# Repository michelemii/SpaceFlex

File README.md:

# SpaceFlex

<br><br>

## Overview

**SpaceFlex** is a surface-EMG monitoring system designed to help astronauts and crew medical officers detect muscle deterioration early during long space missions. By combining a custom **4-channel analog front-end** with an **ESP32** and a browser-based console, SpaceFlex tracks each muscle day by day and compares it with the astronaut's own baseline, flagging decline before it shows up on the scale.

## Key Features

- ⚡ **Custom EMG front-end** - 4 simultaneous channels with low-noise instrumentation amplifiers and a 20–500 Hz filter chain.
- 🛡️ **Noise rejection** - Right-leg-drive circuit cancelling mains interference at its source
- 🎯 **Simultaneous sampling** - 24-bit ADC digitizing all four channels at the same instant
- 📉 **Kalman filtering** - Clean, smooth signal with much less lag than a moving average
- 🧍 **Interactive anatomical map** - 12 muscle groups coloured by their latest status (nominal, warning, critical)
- 🧠 **Personalized diagnostics** - Absolute thresholds, % change from Day 1 and consecutive-drop detection
- ⚖️ **Body-weight monitoring** - Automatic alerts when weight drops below baseline
- 🌐 **Offline web console** - Runs entirely in the browser via Web Serial API, no server or internet needed

>  **SI disclosure:** some parts of this project were developed with the help of SI tools. See [Use of SI tools](#-use-of-si-tools) for details.
---

## 👥 Team

- **Raffaele Manfrin**
- **Michele Missiroli**
- **Andrea Nucciotti**
- **Vlad Panta**
- **Riccardo Pica**

## 📑 Table of Contents

- [LTspice simulation](#ltspice-simulation)
- [KiCad implementation](#kicad-implementation)
- [Software](#software)
- [How to use SpaceFlex](#how-to-use-spaceflex)

---
<br><br>
## LTspice simulation
This [folder](hardware/simulation/) contains the LTspice simulation of the analog front end of our surface EMG acquisition board. The surface EMG signal is tiny (from a few hundred microvolts to a few millivolts, mostly between 20 and 500 Hz) and sits on top of electrode DC offset, 50 Hz mains interference and noise. The circuit amplifies the difference between two electrodes, removes the offset, limits the band and brings the signal to a level the ADC can read.

We designed and validated the chain in LTspice first, then drew the KiCad schematic with the same values.

### Signal chain

**Input RC filter → INA333 → high pass 20 Hz → low pass 500 Hz → ADC**

The circuit runs from a single 3.3 V supply, with the signal centred on 1.65 V.

| Stage | Gain | Pole frequency |
|---|---|---|
| Input RC filter | 1 | 796 kHz |
| INA333 instrumentation amplifier | 5.03 | |
| Sallen Key high pass | 2 | 20 Hz |
| MFB low pass | −10 | 498 Hz |
| **Total** | **≈ 100 (40 dB)** | **band 20 Hz to 500 Hz** |

### Stages and main formulas

#### Input RC filter

R3 = R4 = 1 kΩ and C1 = 100 pF filter out radio frequency interference (phones, WiFi, the ESP32's own radio) before it reaches the amplifier:

```math
f_c = \frac{1}{2\pi\,(R_3+R_4)\,C_1} \approx 796\ \mathrm{kHz}
```

This is far above the EMG band, so the signal is not affected.

#### INA333

The instrumentation amplifier takes the difference between the two electrodes. Its gain is set by RG = RGA + RGB = 24.8 kΩ:

```math
G_{\mathrm{INA}} = 1 + \frac{100\ \mathrm{k\Omega}}{R_G} \approx 5.03
```

The gain is kept low on purpose, so that the electrode DC offset cannot saturate the INA333 before the high pass removes it. The REF pin goes to VREF, so the output sits at 1.65 V. The midpoint between RGA and RGB (`CM_DRL`) will drive the future right leg drive (RLD) circuit.

#### VREF generator

With a single supply, the signal must swing around mid supply. R1 = R2 = 100 kΩ divide the 3.3 V into VREF = 1.65 V, and C7 = 10 µF with C8 = 100 nF filter supply noise:

```math
\tau = (R_1 \parallel R_2)(C_7 + C_8) \approx 0.5\ \mathrm{s}
```

```math
f_c = \frac{1}{2\pi\tau} \approx 0.32\ \mathrm{Hz}
```

An LTC6082 used as a follower buffers VREF, so the INA333 and the filters see a low impedance reference.

#### High pass filter, 20 Hz, gain 2

A second order Sallen Key filter removes the electrode DC offset and the motion artifacts below 20 Hz. With CH1 = CH2 = C = 100 nF, RH1 = 90.9 kΩ, RH2 = 69.8 kΩ and RK1 = RK2 = 10 kΩ:

```math
f_0 = \frac{1}{2\pi\,C\,\sqrt{R_{H1}R_{H2}}} \approx 20\ \mathrm{Hz}
```

```math
K = 1 + \frac{R_{K2}}{R_{K1}} = 2
```

The values give a Butterworth response (Q ≈ 0.71), so the pass band is flat.

#### Low pass filter, 500 Hz, gain −10

A second order multiple feedback (MFB) filter cuts the noise above the EMG band and prevents aliasing at the ADC. With R7 = 2.26 kΩ, R8 = 2.05 kΩ, R9 = 22.6 kΩ, C5 = 220 nF and C6 = 10 nF:

```math
f_0 = \frac{1}{2\pi\sqrt{R_8 R_9 C_5 C_6}} \approx 498\ \mathrm{Hz}
```

```math
H_0 = -\frac{R_9}{R_7} = -10
```

This is also a Butterworth response (Q ≈ 0.71).

#### Total gain

```math
G_{\mathrm{tot}} = G_{\mathrm{INA}} \cdot K \cdot |H_0| \approx 5.03 \cdot 2 \cdot 10 \approx 100 \quad (40\ \mathrm{dB})
```

### AC simulation

The simulation is a frequency sweep from 1 Hz to 100 kHz (`.ac dec 200 1 100k`), with the INA333 model loaded by `.lib INA333.lib`. V1 and V2 have `AC 0.5`, one in phase and one at 180°, so the difference E1 − E2 is 1 V: the plot of `V(OUT)` in dB is directly the gain of the chain.

What you should see:

* about **40 dB (×100)** in the useful band;
* **−3 dB at 19.9 Hz and at 498 Hz**;
* about 28 dB at 1 kHz, with a slope of 40 dB per decade on both sides of the band;
* at 50 Hz the gain is still 40 dB: the filter does not attenuate mains interference, the RLD will reduce it.

### Test with recorded EMG signals

`EMG_E1_LTspice.txt` and `EMG_E2_LTspice.txt` contain a real surface EMG recording, one file per electrode: 2.5 s sampled at 2048 Hz, with a differential signal of up to about 10 mV.

To run this test:

1. In V1, choose **Advanced → PWL FILE** and select `EMG_E1_LTspice.txt`; do the same for V2 with `EMG_E2_LTspice.txt`.
2. Comment out the `.ac` directive and add `.tran 2.7`.
3. Run and plot `V(OUT)`.

What you should see:

* the output is centred on 1.65 V and follows the EMG signal, amplified about 100 times;
* the largest peaks reach about 2.67 V and 0.87 V, well inside the 0 V to 3.3 V range of the ADC;
* when the recording ends at 2.5 s, the output settles back to 1.65 V.

<br><br>

## KiCad implementation

The schematic implements the circuit validated in LTspice, with the same values, repeated for **four identical channels**. On top of the analog chain it adds the parts needed to turn it into a complete board: a right leg drive, an ADC, a microcontroller, separate supplies and protections.

### From the analog chain to the microcontroller

Once each channel has amplified and filtered its signal, the four outputs go to an **ADS131E04**, a 24 bit ADC that samples all four channels at the same instant. VREF goes to the negative input of every ADC channel, so the converter only sees the signal.

The ADC sends the samples to an **ESP32 DevKitC** over **SPI**. A data ready line tells the ESP32, through an interrupt, when a new set of samples is available.

### Right leg drive

The midpoint of each INA333 gain resistor carries the common mode voltage of that channel. A summing amplifier adds the four signals, inverts them and drives the body through the reference electrode:

```math
G_{\mathrm{RLD}} = -\frac{1\ \mathrm{M\Omega}}{390\ \mathrm{k\Omega}} \approx -2.56 \ \text{per channel}
```

This is what attenuates the 50 Hz interference that the filters alone do not remove. A 1 MΩ resistor in series with the output limits the current through the body to a few microamps.

### Separate analog and digital supplies

The analog and digital parts are powered separately, so that the noise of the microcontroller does not reach the amplifiers:

* **+3.3V_A** (analog) comes from an external 3.3 V supply on a screw terminal and powers the amplifiers, the filters, the reference and the analog side of the ADC;
* **+3.3V_D** (digital) comes from the 3.3 V regulator of the ESP32 board and powers the digital side of the ADC.

Every chip has its own decoupling capacitors.

### Protection

* **ESD:** diode arrays on the electrode lines divert electrostatic discharges before they reach the amplifier inputs.
* **EMI:** a metal shield, soldered to ground on the PCB, covers the analog section to keep out the radio interference of the ESP32 and of nearby devices.

## External libraries

| Folder | Content | Source |
|---|---|---|
| `ADS131E04_KiCad/` | ADS131E04 symbol | Made for this project from the [TI datasheet](https://www.ti.com/product/ADS131E04) |
| `Espressif_KiCad/` | ESP32 DevKitC symbol and footprint | [Espressif KiCad libraries](https://github.com/espressif/kicad-libraries) |
| `RF_Shielding.pretty/` | Shielding can footprints | [KiCad footprint library](https://gitlab.com/kicad/libraries/kicad-footprints) |

> [!CAUTION]
> **Electrical Safety Warning**
>
> The electrodes are connected directly to a person, and the board provides no galvanic isolation.
>
> During testing:
> - Power the board exclusively from a battery.
> - **Never connect the ESP32 to a computer powered from the mains while the electrodes are attached.**

<p align="center">
  
  &nbsp;&nbsp;
  
</p>

<p align="center">
  <em>Left: 3D render of the PCB. Right: PCB routing.</em>
</p>
<br><br>

## Software

SpaceFlex monitors an astronaut's muscle health by comparing electrical activity (sEMG) from day to day. The signal travels from the ESP32 over USB to a website that runs in the browser, with no server.

```
sEMG sensor → ESP32 → USB serial 115200 baud → browser (login.html → index.html)
```

### 1. Web application

The site has two pages linked through the browser's `localStorage`.

**`login.html`** collects the subject's profile: first name, last name, age, gender, reference body weight, clinical status and notes. The data is saved, then the page moves on to `index.html`. Opening `index.html` directly redirects back to the login.

**`index.html`** is the console. It connects to the ESP32 through the Web Serial API (Chrome or Edge) and reads each line in real time. The main screen is the anatomical map with the history:

- Two SVG silhouettes, front and back, with 11 clickable muscle groups. The colour shows the latest measured status:

  | Colour | Status |
  |---|---|
  | light green | not measured |
  | green | normal |
  | amber | decay |
  | red | atrophy |

- Counters of muscles per status, a multi-day chart of the selected muscle showing the drift from Day 1, and a chronological log of the sessions.

### 2. Diagnostic algorithm

At the end of the acquisition window the site computes the mean $\bar{V}$ and the peak $V_{\mathrm{peak}}$ of the 200 samples, then `classifyLongTermMuscleStatus()` compares them with the history of the same muscle.

**Step 1: baseline.** It takes the first historical measurement of that muscle (usually Day 1), $\bar{V}_{\mathrm{baseline}}$.

**Step 2: percentage change** (in %):

$$
\Delta = \frac{\bar{V}_{\mathrm{today}} - \bar{V}_{\mathrm{baseline}}}{\bar{V}_{\mathrm{baseline}}} \times 100
$$

**Step 3: slope.** It checks the last two days. Calling $V_{d}$ today's value, $V_{d-1}$ yesterday's and $V_{d-2}$ the day before, if $V_{d} < V_{d-1} < V_{d-2}$ the counter $N_{\mathrm{drops}}$ (`consecutiveDrops`) reaches 2.

**Step 4: decision**, starting from the worst case.

| Status | Condition (any one is enough) |
|---|---|
| **Critical** | $\bar{V} < 2.00\ \mathrm{mV}$ or $\Delta \le -25$ |
| **Warning** | $\bar{V} < 3.05\ \mathrm{mV}$ or $\Delta \le -12$ or $N_{\mathrm{drops}} \ge 2$ |
| **Nominal** | none of the above |

So a muscle at 3.25 mV, which is still above the absolute threshold, turns yellow if it has dropped by 14 % from Day 1.

### 3. Stored data

Everything is kept in a JSON object in `localStorage`, with one key per patient (for example `spaceflex_history_valerio_moretti`):

```json
{
  "currentDay": 15,
  "consumedKcal": 1850,
  "consumedProt": 82,
  "weightHistory": [{ "day": 1, "weight": 78.0 }, { "day": 15, "weight": 76.5 }],
  "measurements": [{ "day": 15, "muscleKey": "calves", "mean": "3.15",
                     "peak": "3.42", "baselinePct": "-16.0", "status": "warning", "note": "..." }]
}
```

When the page opens, `JSON.parse` rebuilds the object. At each new measurement the site adds an element at the start of `measurements` (`unshift`) and rewrites everything with `JSON.stringify`.

<br><br>

## How to use SpaceFlex

### 1. Sign in
Launch the app and fill in the form: first name, last name, age, sex, starting body weight and health status (**Healthy** or **Sick**). Press **Continue →**. For a quick test, **Fill demo data** fills everything in with a sample subject.

### 2. Anatomical map (first screen)
- The silhouette shows the muscles from the front and the back. The colour shows the status of the latest measurement: **grey** not measured, **green** normal, **yellow** decline, **red** atrophy.
- To select a muscle, click it on the silhouette or use the buttons below.
- The right-hand column shows that muscle's trend chart over the days, with the threshold lines, and the history of all measurements. Clicking a measurement selects the corresponding muscle.
- **Alerts**, at the top, opens the list of warnings. The button turns yellow or red when something needs checking, and clicking a warning takes you straight to that muscle.

### 3. Connect the sensor
Connect the ESP32 via USB and press **Connect sensor**. When the connection succeeds, the firmware version appears at the top. You can still use the simulator without the sensor.

### 4. Take a measurement
- Press **Measure ↓**, or scroll down, to go to the second screen.
- Set the mission day: **+1d** moves to the next day. Then choose the duration (5, 10 or 15 seconds).
- Press **Start**. A pop-up shows where to place the electrodes. Apply them and press **Start now**.
- During the measurement you see the signal in real time. At the end, the mean, peak, change from Day 1 and diagnosis are shown.
- The measurement is saved automatically and the map updates.

**Without the sensor:** choose a profile from the simulator menu. Alternatively, type values in mV in the **Manual** field, press **+ Add** and then **Save**.

### 5. Body weight and nutrition (second screen, right side)
- **Nutrition:** enter calories and protein and press **+ Log** to update the daily target bars.
- **Body mass:** enter the day and the weight and press **+**. The table shows the difference from the starting weight and flags excessive drops.

### 6. Alerts
If a measurement or a weight crosses a threshold, a notification appears in the bottom-right corner. Clicking it opens the full list of alerts.

### 7. Sign out or change subject
Press **Sign out** to return to the sign-in screen.

<br><br>

## 🤖 Use of SI tools

In line with the NASA Space Apps Challenge rules, we used SI tools (Claude) in the following parts of the project:

- **Images** - The electrode-placement images were generated with SI tools and carry a visible "SI-generated" watermark.
- **Research** - Support in gathering information on EMG electrode placement (SENIAM guidelines), component selection and scientific literature.
- **Hardware design support** - Assistance in reviewing the schematic and troubleshooting the circuit design.

All design choices were reviewed and validated by the team. No NASA logos, branding or mission identifiers were generated or modified with SI tools.

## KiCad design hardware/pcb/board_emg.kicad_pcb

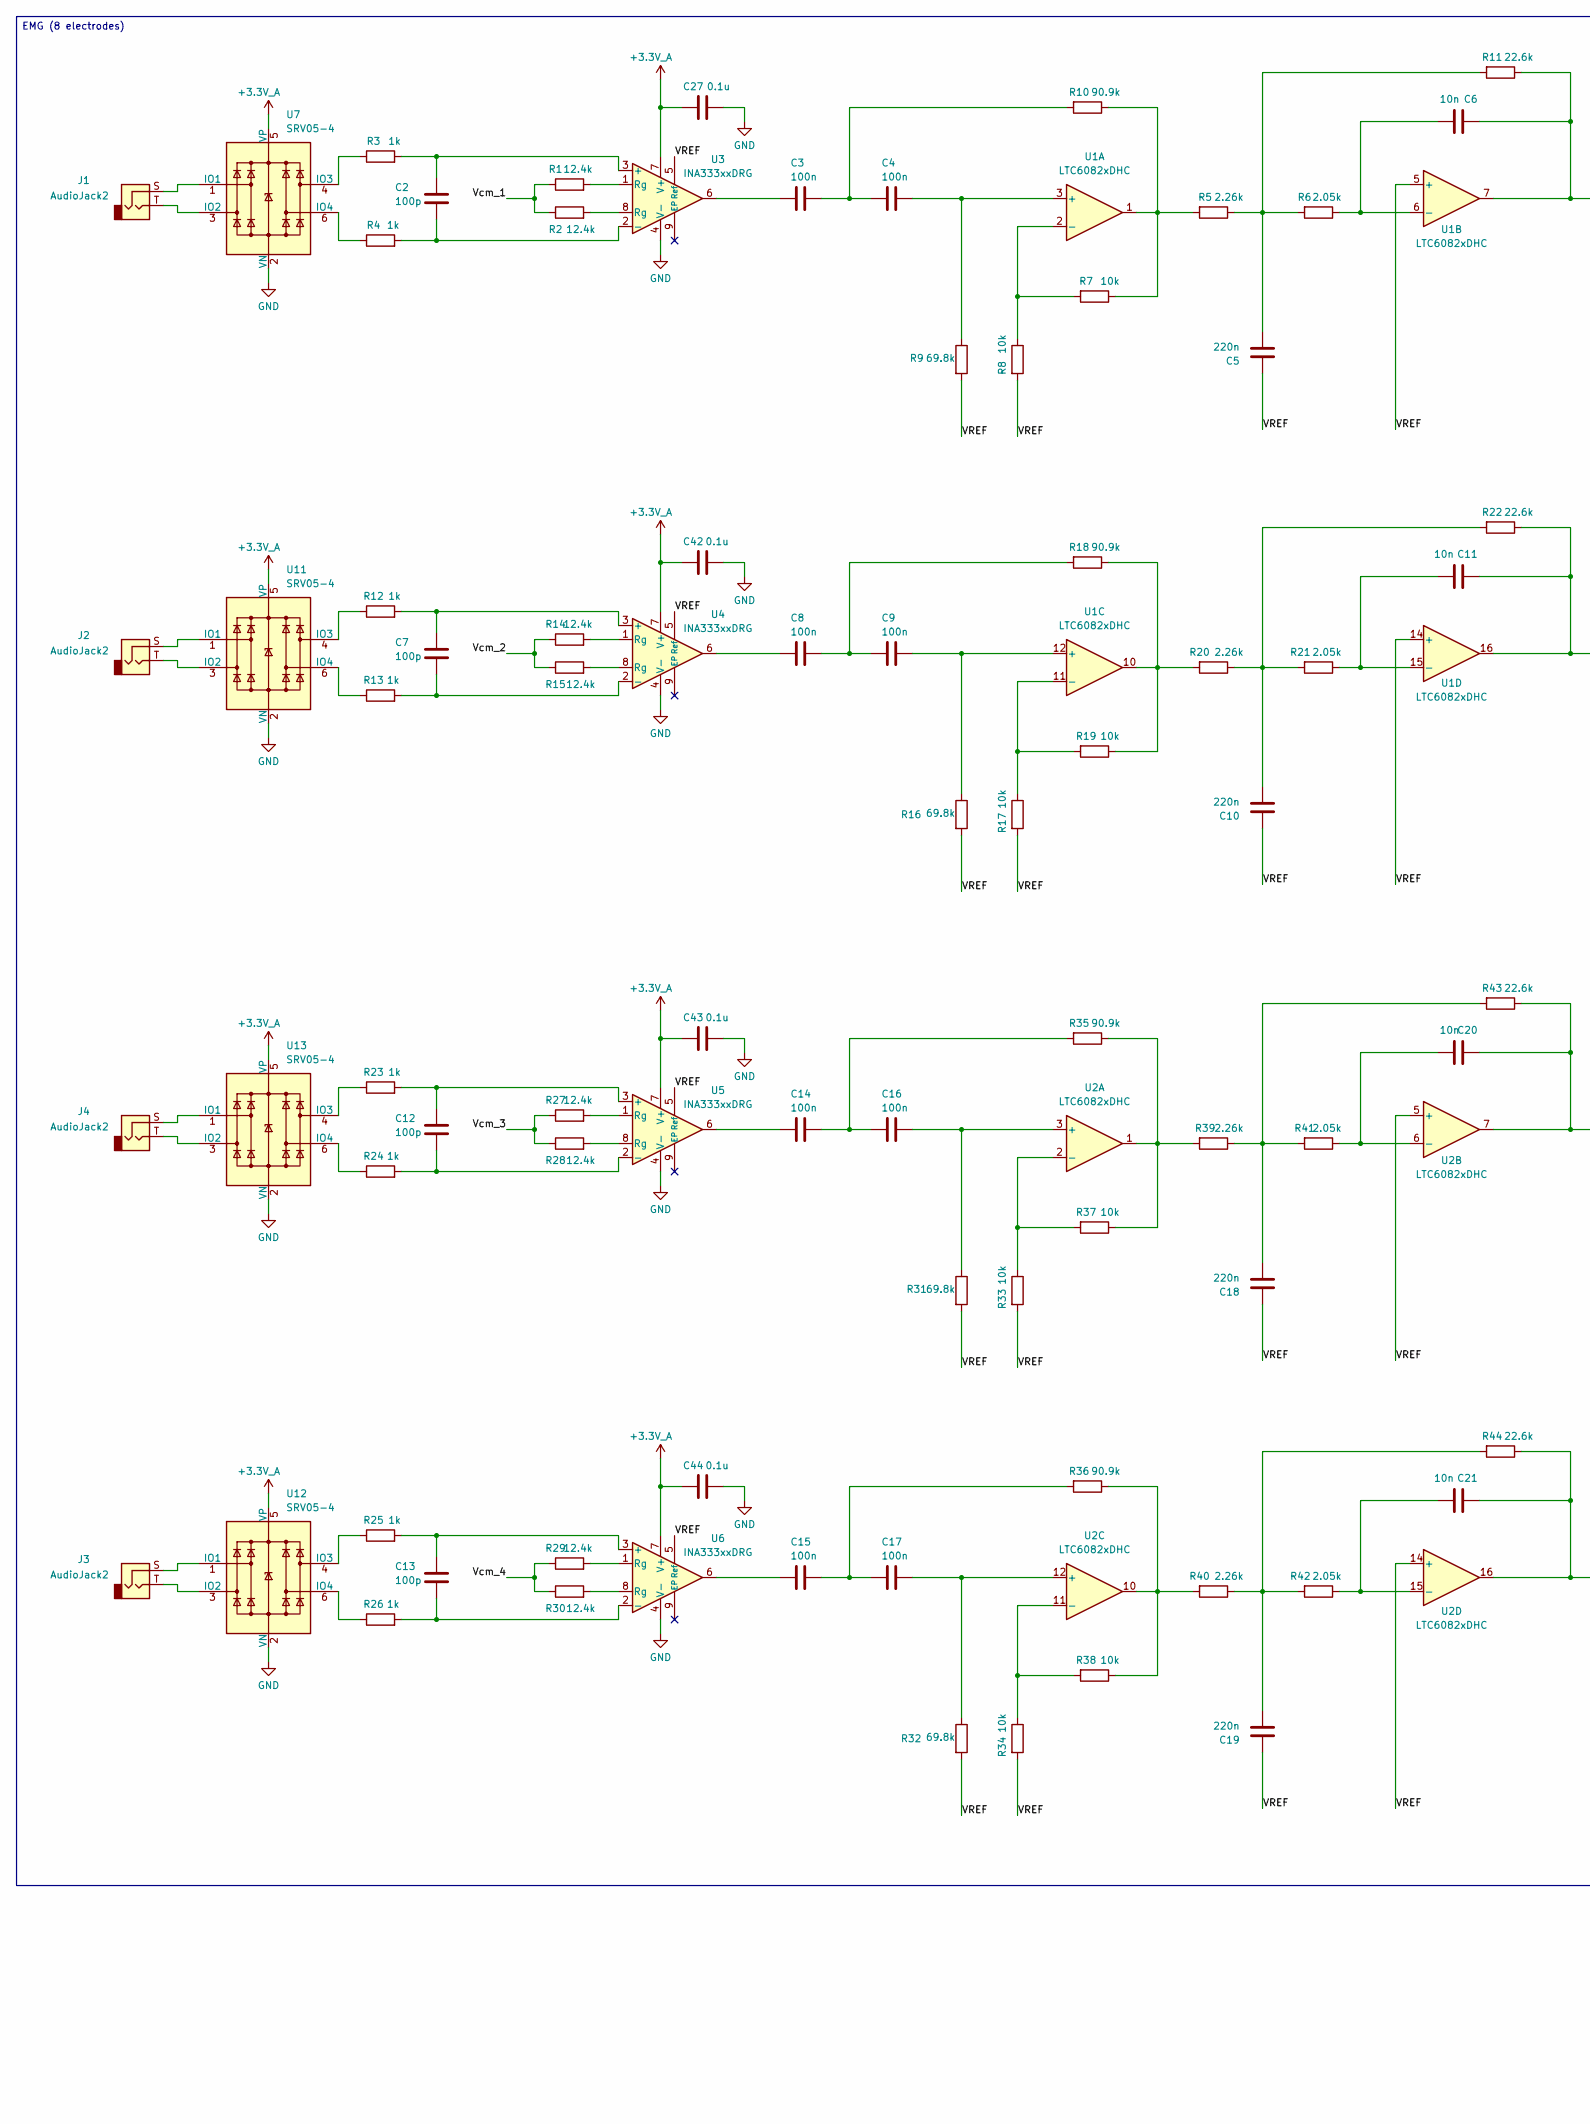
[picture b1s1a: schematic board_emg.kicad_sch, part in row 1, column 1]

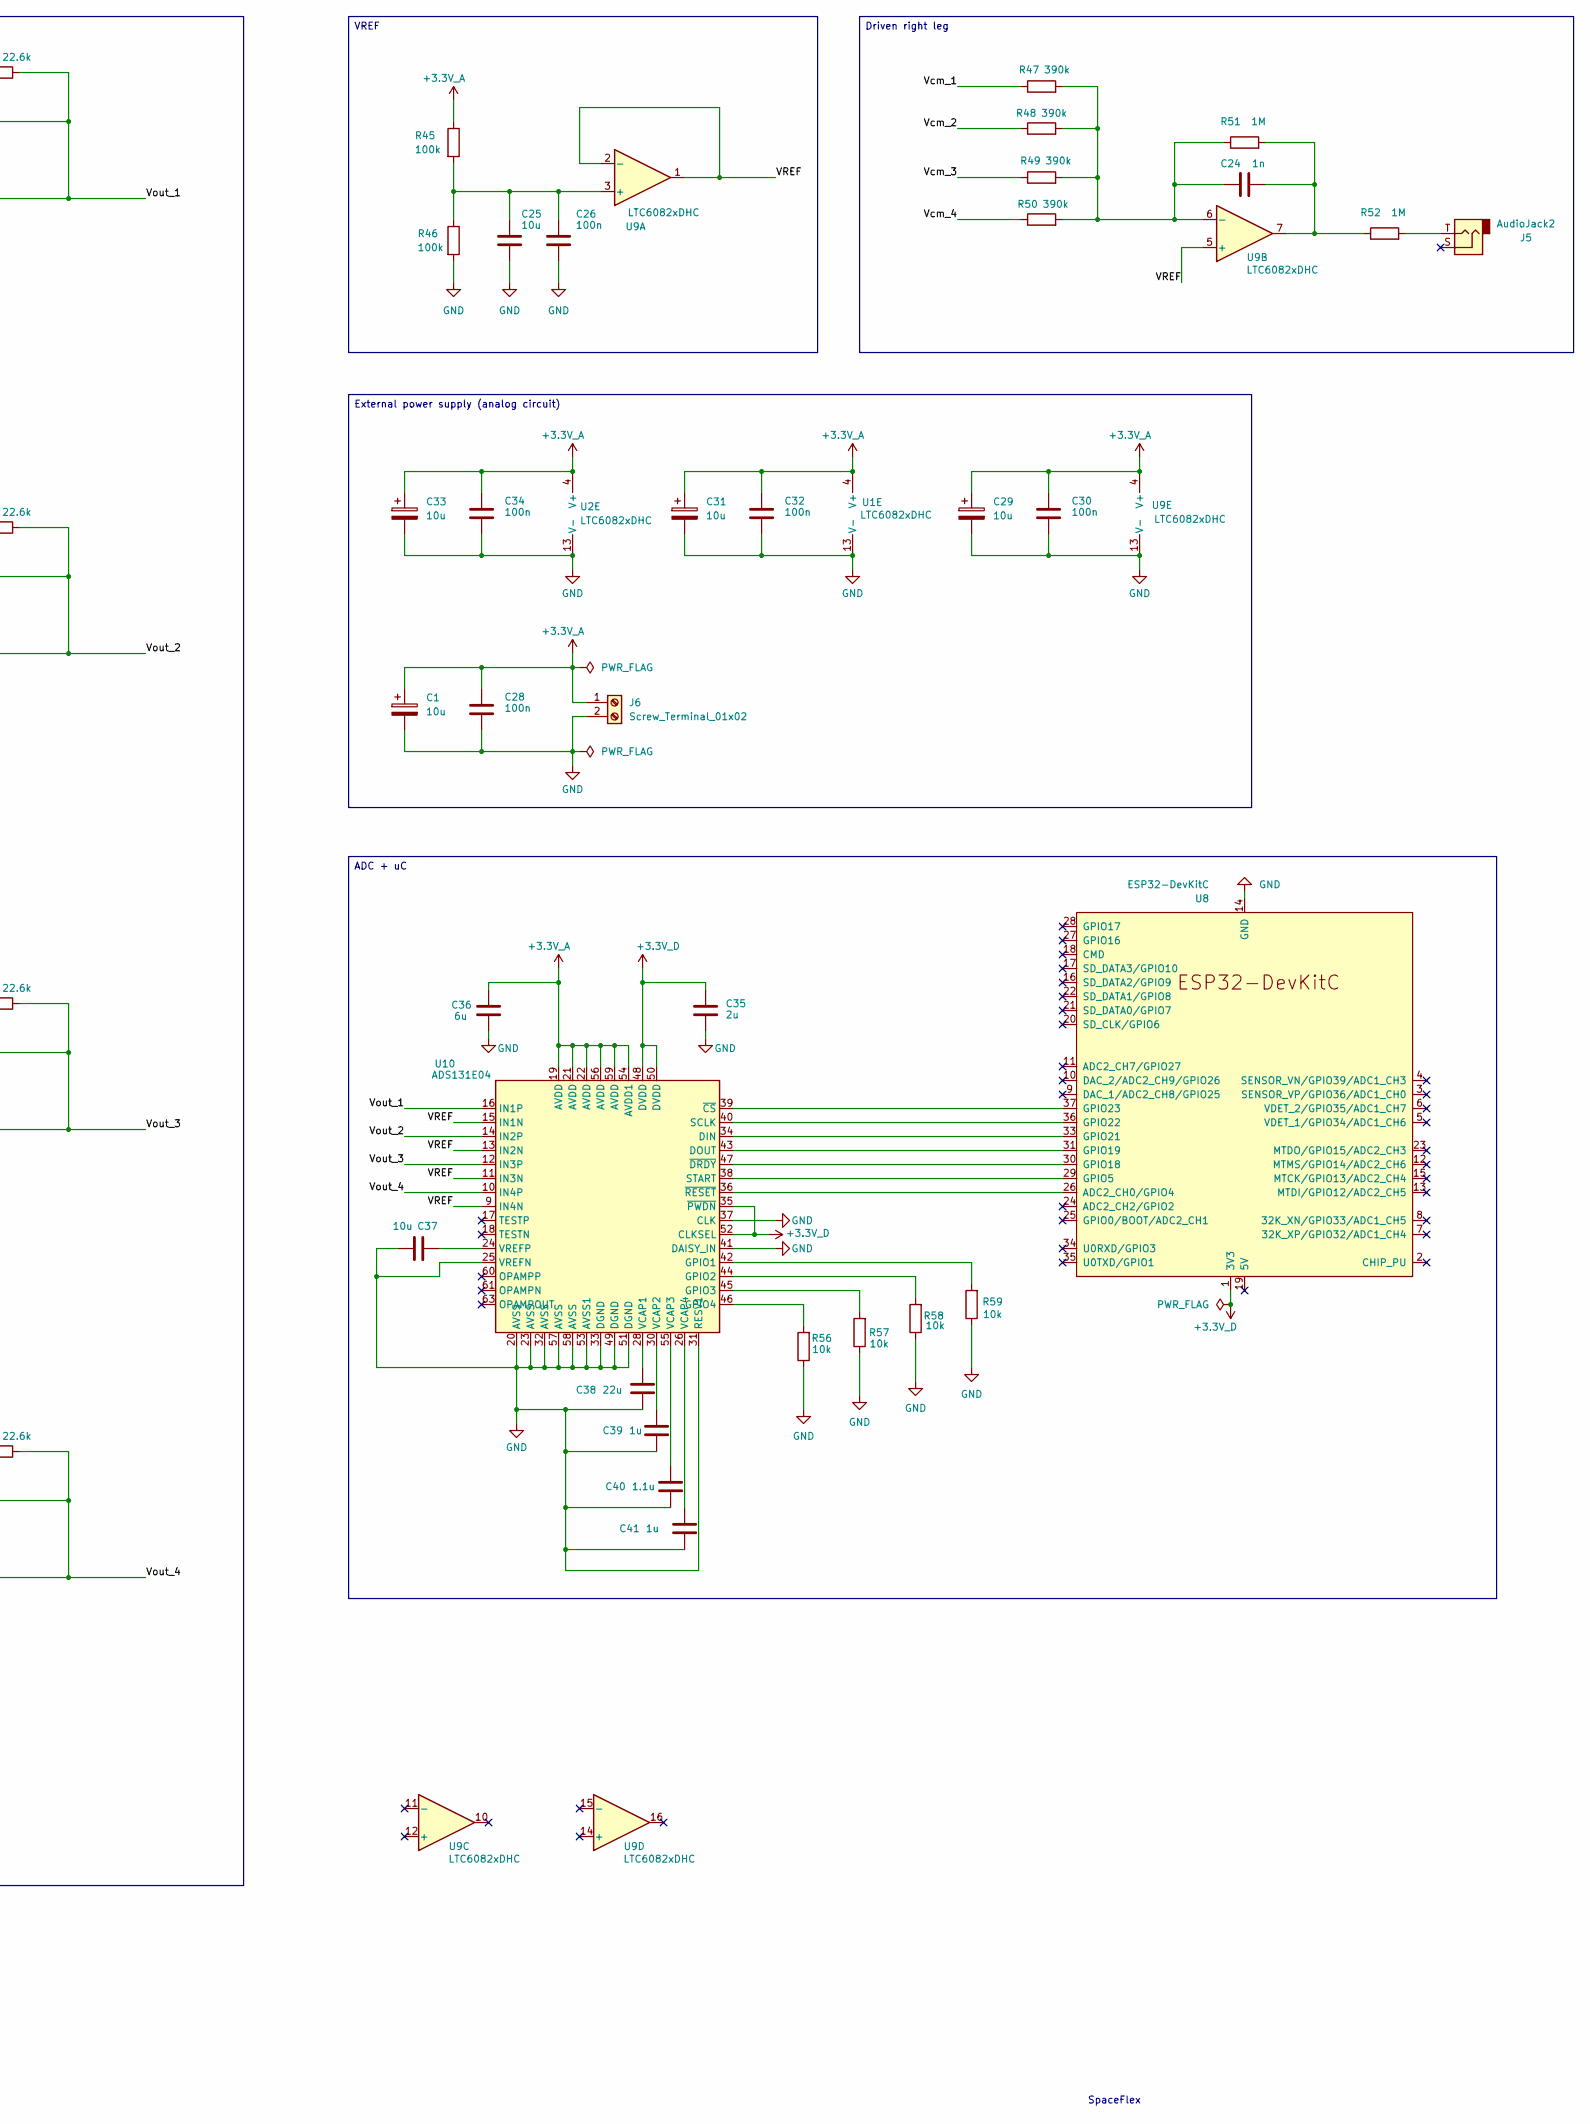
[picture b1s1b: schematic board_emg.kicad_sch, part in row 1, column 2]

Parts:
C1, C29, C31, C33: 10u; CP_Elec_10x10
C2, C7, C12, C13: 100p; C_0402_1005Metric
C3, C4, C8, C9, C14, C15, C16, C17, C26, C28, C30, C32, C34: 100n; C_0402_1005Metric
C5, C10, C18, C19: 220n; C_0402_1005Metric
C6, C11, C20, C21: 10n; C_0402_1005Metric
C24: 1n; C_0402_1005Metric
C25, C37: 10u; C_0402_1005Metric
C27, C42, C43, C44: 0.1u; C_0402_1005Metric
C35: 2u; C_0402_1005Metric
C36: 6u; C_0402_1005Metric
C38: 22u; C_0402_1005Metric
C39, C41: 1u; C_0402_1005Metric
C40: 1.1u; C_0402_1005Metric
J1, J2, J3, J4, J5: AudioJack2; Jack_3.5mm_CUI_SJ-3523-SMT_Horizontal
J6: Screw_Terminal_01x02; PhoenixContact_GMSTBA_2,5_2-G_1x02_P7.50mm_Horizontal
R1, R2, R14, R15, R27, R28, R29, R30: 12.4k; R_0402_1005Metric
R3, R4, R12, R13, R23, R24, R25, R26: 1k; R_0402_1005Metric
R5, R20, R39, R40: 2.26k; R_0402_1005Metric
R6, R21, R41, R42: 2.05k; R_0402_1005Metric
R7, R8, R17, R19, R33, R34, R37, R38, R56, R57, R58, R59: 10k; R_0402_1005Metric
R9, R16, R31, R32: 69.8k; R_0402_1005Metric
R10, R18, R35, R36: 90.9k; R_0402_1005Metric
R11, R22, R43, R44: 22.6k; R_0402_1005Metric
R45, R46: 100k; R_0402_1005Metric
R47, R48, R49, R50: 390k; R_0402_1005Metric
R51, R52: 1M; R_0402_1005Metric
U1, U2, U9: LTC6082xDHC; DFN-16-1EP_3x5mm_P0.5mm_EP1.66x4.4mm
U3, U4, U5, U6: INA333xxDRG; WSON-8-1EP_3x3mm_P0.5mm_EP1.45x2.4mm
U7, U11, U12, U13: SRV05-4; SOT-23-6
U8: ESP32-DevKitC
U10: ADS131E04; TQFP-64_10x10mm_P0.5mm

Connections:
+3.3V_A: C1.1, C27.1, C28.1, C29.1, C30.1, C31.1, C32.1, C33.1, C34.1, C36.1, C42.1, C43.1, C44.1, J6.1, R45.1, U1.4 (V+), U2.4 (V+), U3.7 (V+), U4.7 (V+), U5.7 (V+), U6.7 (V+), U7.5 (VP), U9.4 (V+), U10.19 (AVDD), U10.21 (AVDD), U10.22 (AVDD), U10.54 (AVDD1), U10.56 (AVDD), U10.59 (AVDD), U11.5 (VP), U12.5 (VP), U13.5 (VP)
+3.3V_D: C35.1, U8.1 (3V3), U10.35 (~PWDN), U10.48 (DVDD), U10.50 (DVDD), U10.52 (CLKSEL)
/VREF: C5.2, C10.2, C18.2, C19.2, R8.2, R9.2, R16.2, R17.2, R31.2, R32.2, R33.2, R34.2, U1.5 (+), U1.14 (+), U2.5 (+), U2.14 (+), U3.5 (Ref), U4.5 (Ref), U5.5 (Ref), U6.5 (Ref), U9.1, U9.2 (-), U9.5 (+), U10.9 (IN4N), U10.11 (IN3N), U10.13 (IN2N), U10.15 (IN1N)
/Vcm_1: R1.1, R2.1, R47.1
/Vcm_2: R14.1, R15.1, R48.1
/Vcm_3: R27.1, R28.1, R49.1
/Vcm_4: R29.1, R30.1, R50.1
/Vout_1: C6.1, R11.1, U1.7, U10.16 (IN1P)
/Vout_2: C11.1, R22.1, U1.16, U10.14 (IN2P)
/Vout_3: C20.1, R43.1, U2.7, U10.12 (IN3P)
/Vout_4: C21.1, R44.1, U2.16, U10.10 (IN4P)
GND: C1.2, C25.2, C26.2, C27.2, C28.2, C29.2, C30.2, C31.2, C32.2, C33.2, C34.2, C35.2, C36.2, C37.2, C38.2, C39.2, C40.2, C41.2, C42.2, C43.2, C44.2, J6.2, R46.2, R56.1, R57.1, R58.1, R59.1, U1.13 (V-), U1.17 (V-), U2.13 (V-), U2.17 (V-), U3.4 (V-), U4.4 (V-), U5.4 (V-), U6.4 (V-), U7.2 (VN), U8.14 (GND), U8.32 (GND), U8.38 (GND), U9.13 (V-), U9.17 (V-), U10.20 (AVSS), U10.23 (AVSS), U10.25 (VREFN), U10.31 (RESV1), U10.32 (AVSS), U10.33 (DGND), U10.37 (CLK), U10.41 (DAISY_IN), U10.49 (DGND), U10.51 (DGND), U10.53 (AVSS1), U10.57 (AVSS), U10.58 (AVSS), U11.2 (VN), U12.2 (VN), U13.2 (VN)
unnamed: C3.1, C4.2, R10.2
unnamed: C3.2, U3.6
unnamed: C5.1, R5.1, R6.2, R11.2
unnamed: C8.1, C9.2, R18.2
unnamed: C8.2, U4.6
unnamed: C10.1, R20.1, R21.2, R22.2
unnamed: C14.1, C16.2, R35.2
unnamed: C14.2, U5.6
unnamed: C15.1, C17.2, R36.2
unnamed: C15.2, U6.6
unnamed: C18.1, R39.1, R41.2, R43.2
unnamed: C19.1, R40.1, R42.2, R44.2
unnamed: C24.2, R51.2, R52.1, U9.7
unnamed: J5.T, R52.2
unnamed: R1.2, U3.1 (Rg)
unnamed: R2.2, U3.8 (Rg)
unnamed: R5.2, R7.1, R10.1, U1.1
unnamed: R14.2, U4.1 (Rg)
unnamed: R15.2, U4.8 (Rg)
unnamed: R18.1, R19.1, R20.2, U1.10
unnamed: R27.2, U5.1 (Rg)
unnamed: R28.2, U5.8 (Rg)
unnamed: R29.2, U6.1 (Rg)
unnamed: R30.2, U6.8 (Rg)
unnamed: R35.1, R37.1, R39.2, U2.1
unnamed: R36.1, R38.1, R40.2, U2.10
unnamed: C4.1, R9.1, U1.3 (+)
unnamed: R7.2, R8.1, U1.2 (-)
unnamed: C6.2, R6.1, U1.6 (-)
unnamed: C9.1, R16.1, U1.12 (+)
unnamed: R17.1, R19.2, U1.11 (-)
unnamed: C11.2, R21.1, U1.15 (-)
unnamed: C16.1, R31.1, U2.3 (+)
unnamed: R33.1, R37.2, U2.2 (-)
unnamed: C20.2, R41.1, U2.6 (-)
unnamed: C17.1, R32.1, U2.12 (+)
unnamed: R34.1, R38.2, U2.11 (-)
unnamed: C21.2, R42.1, U2.15 (-)
unnamed: C2.1, R3.2, U3.3 (+)
unnamed: C2.2, R4.2, U3.2 (-)
unnamed: C7.1, R12.2, U4.3 (+)
unnamed: C7.2, R13.2, U4.2 (-)
unnamed: C12.1, R23.2, U5.3 (+)
unnamed: C12.2, R24.2, U5.2 (-)
unnamed: C13.1, R25.2, U6.3 (+)
unnamed: C13.2, R26.2, U6.2 (-)
unnamed: J1.S, U7.1 (IO1)
unnamed: J1.T, U7.3 (IO2)
unnamed: R3.1, U7.4 (IO3)
unnamed: R4.1, U7.6 (IO4)
unnamed: C25.1, C26.1, R45.2, R46.1, U9.3 (+)
unnamed: C24.1, R47.2, R48.2, R49.2, R50.2, R51.1, U9.6 (-)
unnamed: U8.33 (GPIO21), U10.34 (DIN)
unnamed: U8.31 (GPIO19), U10.43 (DOUT)
unnamed: R59.2, U10.42 (GPIO1)
unnamed: R58.2, U10.44 (GPIO2)
unnamed: R57.2, U10.45 (GPIO3)
unnamed: R56.2, U10.46 (GPIO4)
unnamed: U8.36 (GPIO22), U10.40 (SCLK)
unnamed: U8.29 (GPIO5), U10.38 (START)
unnamed: C38.1, U10.28 (VCAP1)
unnamed: C39.1, U10.30 (VCAP2)
unnamed: C40.1, U10.55 (VCAP3)
unnamed: C41.1, U10.26 (VCAP4)
unnamed: C37.1, U10.24 (VREFP)
unnamed: U8.37 (GPIO23), U10.39 (~CS)
unnamed: U8.30 (GPIO18), U10.47 (~DRDY)
unnamed: U8.26 (ADC2_CH0/GPIO4), U10.36 (~RESET)
unnamed: J2.S, U11.1 (IO1)
unnamed: J2.T, U11.3 (IO2)
unnamed: R12.1, U11.4 (IO3)
unnamed: R13.1, U11.6 (IO4)
unnamed: J3.S, U12.1 (IO1)
unnamed: J3.T, U12.3 (IO2)
unnamed: R25.1, U12.4 (IO3)
unnamed: R26.1, U12.6 (IO4)
unnamed: J4.S, U13.1 (IO1)
unnamed: J4.T, U13.3 (IO2)
unnamed: R23.1, U13.4 (IO3)
unnamed: R24.1, U13.6 (IO4)

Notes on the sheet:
SpaceFlex
EMG (8 electrodes)
ADC + uC
VREF
Driven right leg
External power supply (analog circuit)

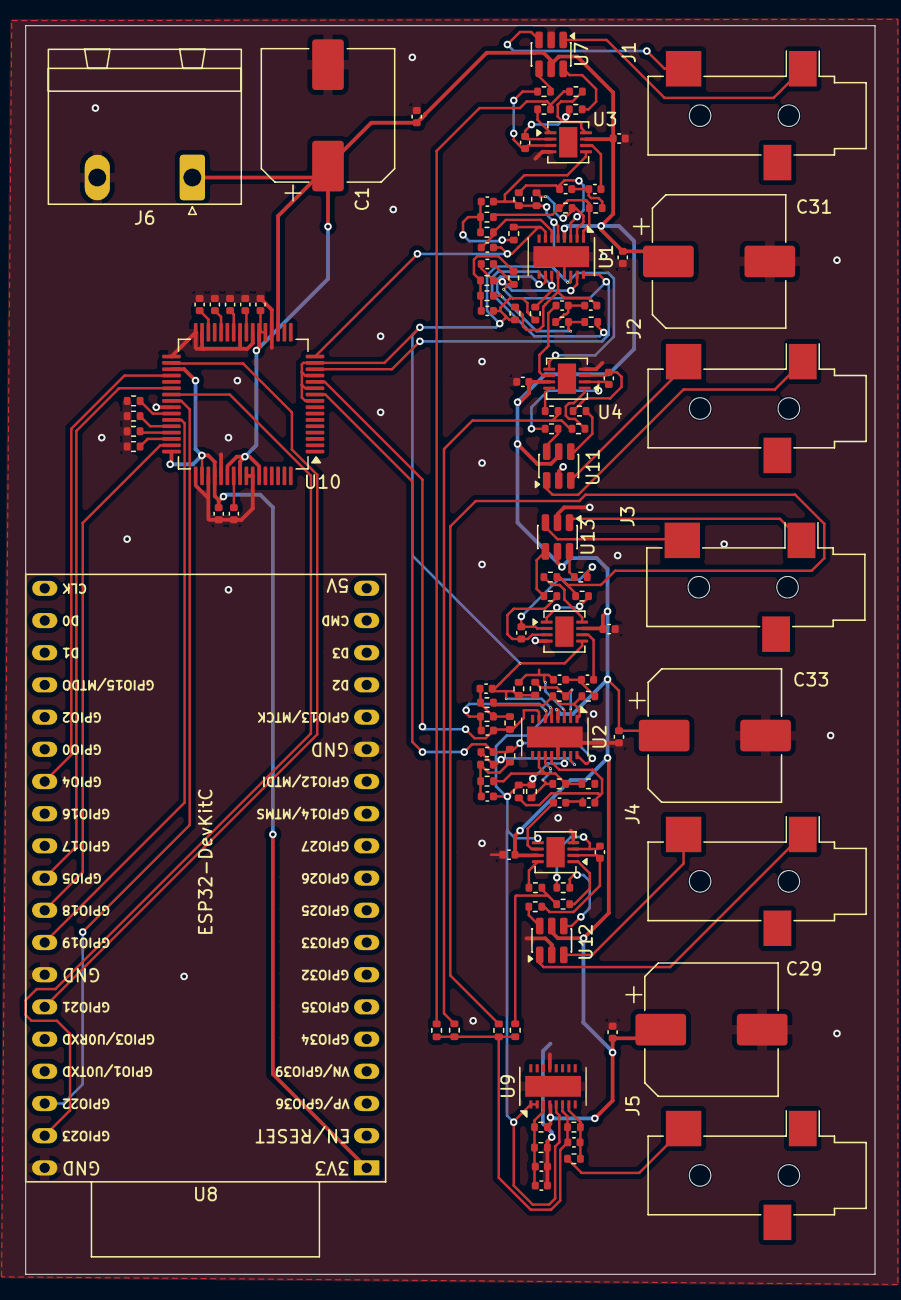
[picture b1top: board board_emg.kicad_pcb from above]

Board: 2 copper layers, 67.0 x 98.5 mm, 117 parts (0 on the bottom side), 92 nets.

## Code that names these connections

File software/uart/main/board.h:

/*
 * board.h
 * Pin map and build time configuration.
 *
 * Pin map taken from the schematic (ESP32 DevKitC U8 <-> ADS131E04 U10):
 *
 *   ADS131E04          ESP32 DevKitC
 *   CS      (pin 39) -> GPIO23
 *   SCLK    (pin 40) -> GPIO22
 *   DIN     (pin 34) -> GPIO21   (ESP32 MOSI)
 *   DOUT    (pin 43) -> GPIO19   (ESP32 MISO)
 *   DRDY    (pin 47) -> GPIO18   (active low, interrupt)
 *   START   (pin 38) -> GPIO5
 *   RESET   (pin 36) -> GPIO4    (active low)
 *   PWDN, CLKSEL     -> +3.3V_D  (hardwired: always on, internal oscillator)
 *   CLK              -> GND      (so CONFIG1.CLK_EN must NEVER be set to 1)
 *   DAISY_IN         -> GND
 *
 * The SPI pins are not the native VSPI IO_MUX pins, so the signals go through
 * the GPIO matrix. That is fine up to well above the SCLK used here.
 */
#pragma once

/* ---------------- ADS131E04 pins ---------------- */
#define PIN_ADS_CS      23
#define PIN_ADS_SCLK    22
#define PIN_ADS_DIN     21   /* ESP32 MOSI */
#define PIN_ADS_DOUT    19   /* ESP32 MISO */
#define PIN_ADS_DRDY    18
#define PIN_ADS_START   5
#define PIN_ADS_RESET   4

/* ---------------- SPI ----------------
 * ADS131E0x: tSCLK min = 50 ns (20 MHz) with DVDD 2.7 V to 3.6 V.
 * 8 MHz leaves a large timing margin through the GPIO matrix; a full RDATA
 * read (opcode + status + 4 x 24 bit) takes 16 us, well inside the 31 us
 * period of the fastest supported rate.
 */
#define ADS_SPI_HOST    SPI3_HOST
#define ADS_SPI_HZ      8000000

/* ---------------- UART to PC ----------------
 * UART0 is the USB bridge of the DevKitC (GPIO1 TX, GPIO3 RX).
 * 921600 works with both CP2102 and CP2102N bridges.
 * If your DevKitC has a CP2102N you can use 2000000 (set the same value in
 * the PC script with --baud). Higher baud = higher sample rates allowed.
 */
#define PC_UART_NUM     UART_NUM_0
#define PC_UART_BAUD    921600

/* Fraction of the UART capacity the firmware accepts to use (percent).
 * A START request that would need more is rejected with ST_BANDWIDTH. */
#define PC_UART_MAX_LOAD_PCT  85

/* ---------------- ADS131E04 analog setup ----------------
 * AVDD = 3.3 V on this board, so only the 2.4 V internal reference is legal
 * (VREF_4V = 1 requires a 5 V analog supply).
 */
#define ADS_VREF_MV     2400

/* Power up wait before the first RESET pulse. The datasheet flow chart waits
 * for the supplies and VCAP1 (22 uF) to settle; 1 s is the flow chart value. */
#define ADS_POWERUP_WAIT_MS   1000

/* Internal reference settling after PDB_REFBUF = 1 (datasheet: 150 ms typ). */
#define ADS_REF_SETTLE_MS     200

/* OFFSETCAL duration (datasheet: 153 ms) plus margin. */
#define ADS_OFFSETCAL_MS      200

/* Firmware version reported in the INFO frame. */
#define FW_VERSION_MAJOR 1
#define FW_VERSION_MINOR 0

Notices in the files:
README.md:
Hardware license
https://img.shields.io/badge/Firmware%20license-GPL%20v3-blue
